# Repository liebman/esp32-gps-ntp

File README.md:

# This is an ESP32 NTP Server with DS3231 synched to GPS PPS signal

**NOTE: This is functional but *very much* a work in progress at the moment.**

This is an [esp-idf](https://docs.espressif.com/projects/esp-idf/en/latest/esp32/index.html) app using [platformio](https://platformio.org/).

## Some details

Synching the DS3231 to the GPS is done with a small high level (level 5) interrupt handler in assembly.  This generates a timestamp and offset in microseconds tracking the active edges of the GPS PPS and RTC SQW signals.  This data is then fed in to a PID algorithm that will generate an offset value used to speed up and slow down the DS3231 RTC.  This keeps the DS3231 synced with the GPS to within a couple of microseconds.  As a side benifit it also tunes the DS3231's ocilator to reduce drift when GPS is unavailable.

- [main](main) Contains the code
- [kicad/esp-gps-ntp](kicad/esp-gps-ntp) contains the schematic and board designs in KiCad.
- [kicad/display-adapter](kicad/display-adapter) contains the schematic and board design for a small adapter to config a single inline header connector to an IDC connector (for ribbon cable connection of display)

The display I'm using is [here](https://www.amazon.com/gp/product/B073R7BH1B)

## Schematic

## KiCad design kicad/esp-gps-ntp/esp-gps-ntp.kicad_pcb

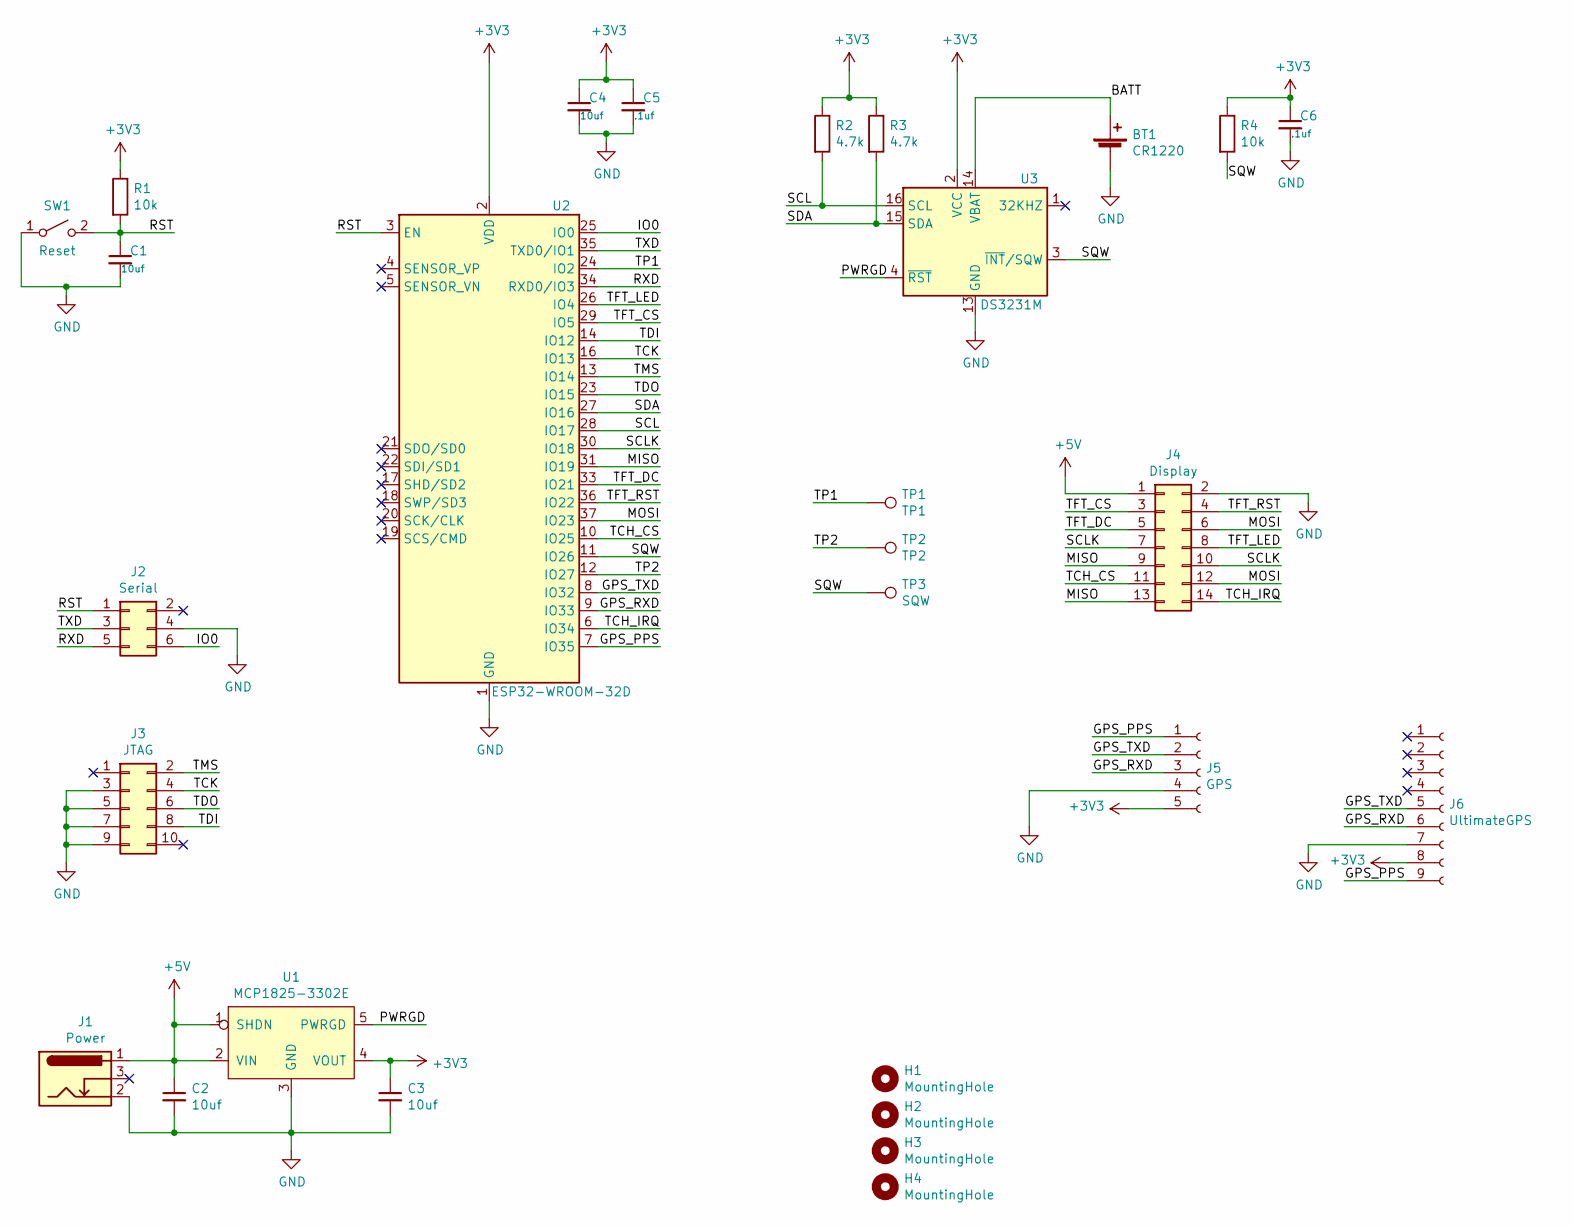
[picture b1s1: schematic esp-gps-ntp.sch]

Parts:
BT1: CR1220; HARWIN-CR1220
C1, C2, C3, C4: 10uf; C_Disc_D5.0mm_W2.5mm_P5.00mm
C5, C6: .1uf; C_Disc_D5.0mm_W2.5mm_P2.50mm
H1, H2, H3, H4: MountingHole; MountingHole_3.2mm_M3
J1: Power; BarrelJack_Horizontal
J2: Serial; IDC-Header_2x03_P2.54mm_Vertical
J3: JTAG; IDC-Header_2x05_P2.54mm_Vertical
J4: Display; IDC-Header_2x07_P2.54mm_Vertical
J5: GPS; PinSocket_1x05_P2.54mm_Vertical
J6: UltimateGPS; PinSocket_1x09_P2.54mm_Vertical
R1, R4: 10k; R_Axial_DIN0207_L6.3mm_D2.5mm_P7.62mm_Horizontal
R2, R3: 4.7k; R_Axial_DIN0207_L6.3mm_D2.5mm_P7.62mm_Horizontal
SW1: Reset; SW_PUSH_6mm
TP1: TP1; TestPoint_THTPad_2.5x2.5mm_Drill1.2mm
TP2: TP2; TestPoint_THTPad_2.5x2.5mm_Drill1.2mm
TP3: SQW; TestPoint_THTPad_2.5x2.5mm_Drill1.2mm
U1: MCP1825-3302E; SOT-223-6
U2: ESP32-WROOM-32D; ESP32-WROOM-32
U3: DS3231M; SOIC-16W_7.5x10.3mm_P1.27mm

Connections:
+3V3: C3.1, C4.1, C5.1, C6.1, J5.5, J6.8, R1.1, R2.1, R3.1, R4.1, U1.4 (VOUT), U2.2 (VDD), U3.2 (VCC)
+5V: C2.1, J1.1, J4.1, U1.1 (SHDN), U1.2 (VIN)
/BATT: BT1.1 (+), U3.14 (VBAT)
/GPS_PPS: J5.1, J6.9, U2.7 (IO35)
/GPS_RXD: J5.3, J6.6, U2.9 (IO33)
/GPS_TXD: J5.2, J6.5, U2.8 (IO32)
/IO0: J2.6, U2.25 (IO0)
/MISO: J4.9, J4.13, U2.31 (IO19)
/MOSI: J4.6, J4.12, U2.37 (IO23)
/PWRGD: U1.5 (PWRGD), U3.4 (~RST)
/RST: C1.1, J2.1, R1.2, SW1.2 (B), U2.3 (EN)
/RXD: J2.5, U2.34 (RXD0/IO3)
/SCL: R2.2, U2.28 (IO17), U3.16 (SCL)
/SCLK: J4.7, J4.10, U2.30 (IO18)
/SDA: R3.2, U2.27 (IO16), U3.15 (SDA)
/SQW: R4.2, TP3.1, U2.11 (IO26), U3.3 (~INT~/SQW)
/TCH_CS: J4.11, U2.10 (IO25)
/TCH_IRQ: J4.14, U2.6 (IO34)
/TCK: J3.4, U2.16 (IO13)
/TDI: J3.8, U2.14 (IO12)
/TDO: J3.6, U2.23 (IO15)
/TFT_CS: J4.3, U2.29 (IO5)
/TFT_DC: J4.5, U2.33 (IO21)
/TFT_LED: J4.8, U2.26 (IO4)
/TFT_RST: J4.4, U2.36 (IO22)
/TMS: J3.2, U2.13 (IO14)
/TP1: TP1.1, U2.24 (IO2)
/TP2: TP2.1, U2.12 (IO27)
/TXD: J2.3, U2.35 (TXD0/IO1)
GND: BT1.2 (-), C1.2, C2.2, C3.2, C4.2, C5.2, C6.2, J1.2, J2.4, J3.3, J3.5, J3.7, J3.9, J4.2, J5.4, J6.7, SW1.1 (A), U1.3 (GND), U1.6 (GND), U2.1 (GND), U2.15 (GND), U2.38 (GND), U2.39 (GND), U3.5 (GND), U3.6 (GND), U3.7 (GND), U3.8 (GND), U3.9 (GND), U3.10 (GND), U3.11 (GND), U3.12 (GND), U3.13 (GND)

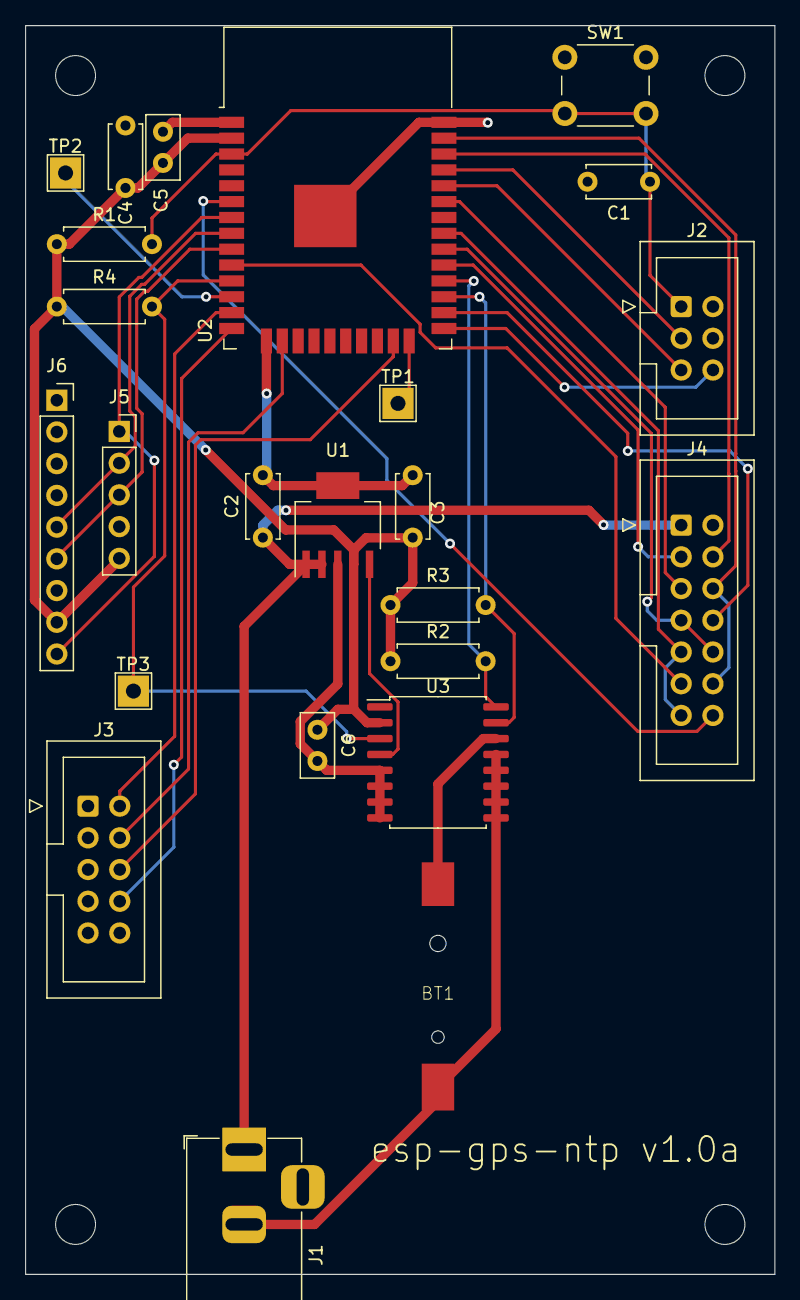
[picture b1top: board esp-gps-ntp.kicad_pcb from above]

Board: 2 copper layers, 60.0 x 100.0 mm, 28 parts (0 on the bottom side), 30 nets.

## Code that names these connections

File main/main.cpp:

/*
 * MIT License
 *
 * Copyright (c) 2020 Christopher B. Liebman
 *
 * Permission is hereby granted, free of charge, to any person obtaining a copy
 * of this software and associated documentation files (the "Software"), to deal
 * in the Software without restriction, including without limitation the rights
 * to use, copy, modify, merge, publish, distribute, sublicense, and/or sell
 * copies of the Software, and to permit persons to whom the Software is
 * furnished to do so, subject to the following conditions:
 *
 * The above copyright notice and this permission notice shall be included in all
 * copies or substantial portions of the Software.
 *
 * THE SOFTWARE IS PROVIDED "AS IS", WITHOUT WARRANTY OF ANY KIND, EXPRESS OR
 * IMPLIED, INCLUDING BUT NOT LIMITED TO THE WARRANTIES OF MERCHANTABILITY,
 * FITNESS FOR A PARTICULAR PURPOSE AND NONINFRINGEMENT. IN NO EVENT SHALL THE
 * AUTHORS OR COPYRIGHT HOLDERS BE LIABLE FOR ANY CLAIM, DAMAGES OR OTHER
 * LIABILITY, WHETHER IN AN ACTION OF CONTRACT, TORT OR OTHERWISE, ARISING FROM,
 * OUT OF OR IN CONNECTION WITH THE SOFTWARE OR THE USE OR OTHER DEALINGS IN THE
 * SOFTWARE.
*/

#include "freertos/FreeRTOS.h"
#include "freertos/task.h"
#include "driver/gpio.h"
#include "nvs_flash.h"
#include "esp_log.h"

#include "Config.h"
#include "Display.h"
#include "Network.h"
#include "DS3231.h"
#include "MicroSecondTimer.h"
#include "PPS.h"
#include "GPS.h"
#include "NTP.h"
#include "SyncManager.h"

#include "PageAbout.h"
#include "PageConfig.h"
#include "PagePPS.h"
#include "PageDelta.h"
#include "PageSync.h"
#include "PageGPS.h"
#include "PageSats.h"
#include "PageNTP.h"

#define LATENCY_PIN 2
#define LATENCY_SEL (1<<LATENCY_PIN)

#ifdef __cplusplus
//
// app_main() is called from C
//
extern "C" {
    void app_main(void);
}
#endif

#if defined(CONFIG_GPSNTP_RTC_DRIFT_MAX)
#define RTC_DRIFT_MAX CONFIG_GPSNTP_RTC_DRIFT_MAX
#else
#define RTC_DRIFT_MAX 500
#endif

#define GPS_RX_PIN (GPIO_NUM_33)
#define GPS_TX_PIN (GPIO_NUM_32)
#define GPS_PPS_PIN ((gpio_num_t)CONFIG_GPSNTP_PPS_PIN)
#define RTC_PPS_PIN ((gpio_num_t)CONFIG_GPSNTP_SQW_PIN)
#define SDA_PIN (GPIO_NUM_16)
#define SCL_PIN (GPIO_NUM_17)
#define TFT_LED_PIN (GPIO_NUM_4)
#define TFT_LED_SEL (GPIO_SEL_4)
#define TCH_IRQ_PIN ((gpio_num_t)CONFIG_LV_TOUCH_PIN_IRQ)
#if CONFIG_LV_TOUCH_PIN_IRQ < 32
#define TCH_IRQ_SEL (1<<CONFIG_LV_TOUCH_PIN_IRQ)
#else
#define TCH_IRQ_SEL ((uint64_t)(((uint64_t)1)<<CONFIG_LV_TOUCH_PIN_IRQ))
#endif

static const char* TAG = "main";


extern pps_data_t rtc_pps_data; // in highint5.S
extern pps_data_t gps_pps_data; // in highint5.S

static Config config;
static MicroSecondTimer usec_timer;
static PPS gps_pps(usec_timer, &gps_pps_data);
static PPS rtc_pps(usec_timer, &rtc_pps_data, &gps_pps); // use gps_pps as ref.
static GPS gps(usec_timer);
static DS3231 rtc;
static NTP ntp(rtc_pps);
static SyncManager syncman(gps, rtc, gps_pps, rtc_pps);

static void apply_config()
{
    ESP_LOGI(TAG, "apply_config()");
    syncman.setBias(config.getBias());
    syncman.setTarget(config.getTarget());
}

static void init(void* data)
{
    (void)data;
    ESP_LOGI(TAG, "init: with priority %d core %d", uxTaskPriorityGet(nullptr), xPortGetCoreID());

    esp_err_t err;
    gpio_config_t io_conf;

#ifdef LATENCY_OUTPUT
    ESP_LOGI(TAG, "configuring LATENCY_PIN pin %d", LATENCY_PIN);
    io_conf.pin_bit_mask = LATENCY_SEL;
    io_conf.mode = GPIO_MODE_OUTPUT;
    io_conf.intr_type = GPIO_INTR_DISABLE;
    io_conf.pull_down_en = GPIO_PULLDOWN_DISABLE;
    io_conf.pull_up_en = GPIO_PULLUP_DISABLE;
    err = gpio_config(&io_conf);
    if (err != ESP_OK)
    {
        ESP_LOGE(TAG, "failed to init LATENCY_PIN pin as output: %d '%s'", err, esp_err_to_name(err));
    }
#endif

    ESP_LOGI(TAG, "init: starting display");
    if (!Display::getDisplay().begin())
    {
        ESP_LOGE(TAG, "init: failed to initialize display!");
    }

    // turn the backlight on.
    ESP_LOGI(TAG,  "turning backlight on");
    io_conf.pin_bit_mask = TFT_LED_SEL;
    io_conf.mode = GPIO_MODE_OUTPUT;
    io_conf.intr_type = GPIO_INTR_DISABLE;
    io_conf.pull_down_en = GPIO_PULLDOWN_DISABLE;
    io_conf.pull_up_en = GPIO_PULLUP_DISABLE;
    err = gpio_config(&io_conf);
    if (err != ESP_OK)
    {
        ESP_LOGE(TAG, "failed to init backlight pin as output: %d '%s'", err, esp_err_to_name(err));
    }
    // turn the backlight on.
    gpio_set_level(TFT_LED_PIN, 1);

    // initialize I2C_NUM_0
    err = i2c_driver_install(I2C_NUM_0, I2C_MODE_MASTER, 0, 0, 0);
    if (err != ESP_OK)
    {
        ESP_LOGE(TAG, "i2c_driver_install: I2C_NUM_%d %d (%s)", I2C_NUM_0, err, esp_err_to_name(err));
    }
    i2c_config_t conf;
    conf.mode = I2C_MODE_MASTER;
    conf.sda_io_num = SDA_PIN;
    conf.scl_io_num = SCL_PIN;
    conf.sda_pullup_en = GPIO_PULLUP_DISABLE;
    conf.scl_pullup_en = GPIO_PULLUP_DISABLE;
    conf.master.clk_speed = 400000;
    err = i2c_param_config(I2C_NUM_0, &conf);
    if (err != ESP_OK)
    {
        ESP_LOGE(TAG, "i2c_param_config: I2C_NUM_%d %d (%s)", I2C_NUM_0, err, esp_err_to_name(err));
    }

    while (!rtc.begin())
    {
        ESP_LOGE(TAG, "failed to start rtc!");
        vTaskDelay(pdMS_TO_TICKS(100));
    }

    // start gps watching NMEA messages
    // swap rx/tx as GPS_RX is our TX!
    if (!gps.begin(GPS_RX_PIN, GPS_TX_PIN))
    {
        ESP_LOGE(TAG, "failed to start gps!");
    }

    // start pps watching gps
    if (!gps_pps.begin(GPS_PPS_PIN))
    {
        ESP_LOGE(TAG, "failed to start GPS pps!");
    }

    // start pps watching rtc
    if (!rtc_pps.begin(RTC_PPS_PIN, true))
    {
        ESP_LOGE(TAG, "failed to start RTC pps!");
    }

    // wait for the RTC PPS signal to be low, the first half of a secondm, so we
    // don't do this on a second boundry as the RTC PPS could get or miss an increment.
    ESP_LOGI(TAG, " waiting a change in seconds");
    time_t now = rtc_pps.getTime(nullptr);
    while(rtc_pps.getTime(nullptr) == now)
    {
        vTaskDelay(pdMS_TO_TICKS(50));
    }
    ESP_LOGI(TAG, "setting time on RTC pps");
    struct tm tm;
    rtc.getTime(&tm);
    rtc_pps.setTime(mktime(&tm));

    // start NTP services
    ntp.begin();

    // start the sync manager
    syncman.begin();

    new PageNTP(ntp, syncman);
    new PagePPS(gps_pps, rtc_pps);
    new PageSync(syncman);
    new PageDelta(syncman);
    new PageGPS(gps);
    new PageSats(gps);
    new PageConfig(config, apply_config);
    new PageAbout();

    vTaskDelete(NULL);
}

void app_main()
{
    ESP_LOGI(TAG, "Starting with priority %d core %d", uxTaskPriorityGet(nullptr), xPortGetCoreID());
    //Initialize NVS
    ESP_LOGI(TAG, "initializing NVS");
    esp_err_t ret = nvs_flash_init();
    if (ret == ESP_ERR_NVS_NO_FREE_PAGES || ret == ESP_ERR_NVS_NEW_VERSION_FOUND) {
      ESP_ERROR_CHECK(nvs_flash_erase());
      ret = nvs_flash_init();
    }
    ESP_ERROR_CHECK(ret);

    config.begin();
    config.load();
    apply_config();

    xTaskCreatePinnedToCore(&init, "init", 4096, nullptr, 1, nullptr, 1);

    ESP_LOGI(TAG, "initializing Network");
    Network::getNetwork().begin(config.getWiFiSSID(), config.getWiFiPassword());

    bool was_valid = false;
    bool is_on = true;

    while(true)
    {
        struct timeval gps_tv;
        gps_pps.getTime(&gps_tv);
        bool now_valid = gps.getValid();
        if (was_valid != now_valid)
        {
            ESP_LOGW(TAG, "gps %s validity!", now_valid ? "gained" : "lost");
            was_valid = now_valid;
        }

        if (Display::getDisplay().getIdleTime() > 3600) // 1 hr
        {
            if (is_on)
            {
                ESP_LOGI(TAG, "turning OFF backlight");
                gpio_set_level(TFT_LED_PIN, 0);
                is_on = false;
            }
        }
        else if (!is_on)
        {
            ESP_LOGI(TAG, "turning ON backlight");
            gpio_set_level(TFT_LED_PIN, 1);
            is_on = true;
        }

        vTaskDelay(pdMS_TO_TICKS(100));
    }
}

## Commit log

2020-09-13 initialial commit
2020-09-13 basic uart reading/logging
2020-09-14 use pattern match
2020-09-14 moved gps io to GPS class
2020-09-14 switching to lvgl master
2020-09-14 gos to 115200 baud
2020-09-15 for now display PSTI
2020-09-15 display time from RMC and ZDA
2020-09-15 added timer, just counting now, no resets.
2020-09-15 fix baud rate for adafruit gps
2020-09-15 small cleanup
2020-09-16 minor adjustment
2020-09-16 use timer to detect missing PPS signals
2020-09-22 increase uart buffer, backlight off timer
2020-09-23 update lvgl to current master v7.6.0+
2020-09-23 remove padding fro GPS page
2020-09-25 include config for GPS type & set baud rate set system time and track current time in seconds
2020-09-26 configure gps type increment time only not short
2020-09-26 track unix time in seconds from pps
2020-09-26 improve pps isr
2020-09-27 Added simple Sats page still WIP
2020-09-27 improve Sat tracked counting graph
2020-09-27 simplify isr's
2020-10-03 configure fort esp32ntp-v0.1 board!
2020-10-03 remove MCP23017
2020-10-03 hacky version setting with DS3231
2020-10-03 fix timer interrupt
2020-10-10 WIP - PPS latency output
2020-10-10 remove small dead code
2020-10-11 make the timer choice configurable in menuconfig
2020-10-11 move microsecond timer out of GPS
2020-10-11 make timer values configurable
2020-10-14 display last short valuye
2020-10-19 change timer to increase only, no interrupts
2020-10-20 only install gpio_install_isr_service once
2020-10-24 sync ds3231 time with PPS from GPS - WIP
2020-10-25 SyncManager now manages time synching
2020-10-25 on startup set PPS time for rtc in first half of second
2020-10-27 WIP working on sync
2020-10-31 wip cleanup before adding wifi & ulp
2020-10-31 updated some stats displayed
2020-11-01 added basic wifi config with hard codded ssid/pass from local.ini
2020-11-01 stubbed out ULP code
2020-11-01 improved network
2020-11-01 screen blanking and add uptime and ip adress to about
2020-11-02 use intr level 3 for pps & disable the level check in teh isr
2020-11-02 start of NTP service
2020-11-02 small getTime cleanup
2020-11-02 basic packet recieve
2020-11-02 basic NTP working!
2020-11-04 for now use ULP for latency pin
2020-11-04 Added RTC
2020-11-06 PPS optionally monitors a ref PPS for offset in usec
2020-11-06 added basic sync manager
2020-11-07 added simple drift compensation (WIP)
2020-11-07 smooth the offset by averaging the last 10
2020-11-07 dont clean the ds3231 adjustments
2020-11-08 fix drift adjustment calculation in DS3231
2020-11-08 some cleanups
2020-11-08 refactor age offset handling
2020-11-08 cleanup drift/adjustment a bit
2020-11-08 switch to drift_adjust
2020-11-08 difference in seconds now causes time set
2020-11-08 include rtc pps statts on PPS page
2020-11-08 Fix logic issue with start/end adjustments
2020-11-12 display delta graph
2020-11-13 use a PID controler to adjust rtc timeing (roughly tuned)
2020-11-14 ds3231 leave age offset alone at startup
2020-11-14 small cleanup (removed unused method
2020-11-14 small comment update
2020-11-14 Add GPS time to sync page
2020-11-14 Delta graphs shows min/max/avg error one point per minute
2020-11-14 show a second graph with error by second
2020-11-15 added config with bias setting
2020-11-15 drop ulp, add stub for high level int 5
2020-11-16 Use direct register access in ISR for GPIO. Use ionly 32 bits from us timer
2020-11-17 added simple task view page
2020-11-17 use a 10us offset for sync
2020-11-17 old sdkconfig updates
2020-11-18 lvgl 7.2 + 30 hour delta graph
2020-11-20 compute and return offset as float
2020-11-21 mark GPS invalid is RMC age > 1.5 seconds
2020-11-21 add GPS validity timeout and valid for rules
2020-11-21 drop me4dian calculation, its not needed
2020-11-26 Update display values based on offset data size
2020-11-26 hack to set time if gps says its different - needs work
2020-11-26 Some tuning, add config apply
2020-11-26 Simple (incomplete) NTP Page
2020-11-27 updated esp32 drivers
2020-11-27 updated drivers
2020-11-27 moving lvgl to master (WIP)
2020-11-27 upgrade to lvgl master (7.8 pre)
2020-11-27 small cleanup for minmea config
2020-12-03 Board 1.0
2020-12-03 ignore step files
2020-12-05 remove unneeded style
2020-12-05 fix keyboard layout/location
2020-12-05 use numeric keyboard for number fields
2020-12-08 hacked, rtc_pps disabled, gps_pps handled with highint5
2020-12-08 use pin number to check interrupt
2020-12-09 support multiple pins in highint5
2020-12-10 fixes for highint + using new board
2020-12-11 sync working with highint5
2020-12-11 implement min/max counting in asm isr (min is broken I think)
2020-12-11 fix check_short
2020-12-13 new board version fix idle time hack
2020-12-14 checkin display adapter
2020-12-14 re-enable idle report
2020-12-19 upgrade platform to pickup newer openocd for esp32 v3
2020-12-19 no need for 32khz, disable it
2020-12-19 use microsecond timer for gps rmc message timestamps
2020-12-19 save/restore SAR register on entry/exit
2020-12-19 add 64 bit value fetch
2020-12-19 log out of rance PPS timings
2020-12-20 minor timestamp change
2020-12-20 use standard esp-idf name for main compnent
2020-12-20 updated lvgl
2020-12-20 protect access to 64 bit fields with a lock
2020-12-23 minor debugging updates
2020-12-23 attempt submodule for drivers
2020-12-23 updated submodule with patch for include
2020-12-24 used fixed touch idle time for backlight on/off
2020-12-25 update lvgl_esp32_drivers
2020-12-26 updated branch for lvgl_cpp
2020-12-26 added MIT License
2020-12-26 updated lvgl_cpp
2020-12-26 create initial readme
2020-12-26 fix README schematic link
2020-12-26 remove NEW_BOARD hack (PPS/SQW pins now in Kconfig)
2020-12-27 initial simple github action for CI
2020-12-27 CI updates
2020-12-27 try with updated path
2020-12-27 use pip3?
2020-12-27 foud example from platformio docs
2020-12-29 update esp32_drivers
2020-12-30 back to master on lvgl_esp32_drivers
2020-12-30 update lvgl to current master
2021-01-02 minor cleanup
2021-01-03 c++ style fixes
2021-01-03 revert Kp value, still could use a better tuning
2021-01-03 minor readme update
2021-01-09 update lvgl
2021-01-16 Improve NTP Display
2021-01-30 fix compile with interrupt_service (only used for some testing)
2022-02-05 return valid only if GPS has been valid for 20 minutes
2022-02-05 add output value to display small cleanups
2022-02-05 gps_pps time is set in SyncManager now remove unused ifdefs
2022-02-05 removed PageTask as it was unused
2022-02-05 remove code no longer needed
2022-02-05 remove unused config options move my local port/uploader to local.ini
2022-02-06 remove unused code
2022-02-06 added wait's when reading the hardware timer registers
